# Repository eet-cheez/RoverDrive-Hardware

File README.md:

# RoverDrive-Hardware
A custom PCB for a robot powered by an esp32 microcontroller that has pins to control 4 servos plus one for sub-micro servo at 3.3v (in case it burns out at 5v). It also can support multiple other devices like LEDs or sensors and has an IMU to know its direction.

### Why am I doing this?
Last year, I built a robot that was controlled by connecting to an app. The problem is that the inside was a mess of wires and modules floating around, so it was a pain to fix and improve. I decided a PCB could fit more features while also being much easier to assemble and access.

## Details
- The microcontroller is an ESP32-S3-mini-1. I only really chose it because it seemed compact, but there are probably much better options. 
- For the IMU, it uses a BNO055, which does all of the calculations internally to find its orientation. Might be a bit overkill, but I want to make sure it works properly.
- The board uses a basic ams1117-3.3 to to power all of the 3.3v devices.
- Power is supplied to the board via a 1s lipo battery, which gets boosted to 5v by a mt3608 regulator.
- PCB designed in KiCad.
### Schematic: 

### PCB: 

#### CAD:
This is that the robot looks like with a model of the PCB (in TinkerCad):

The robot chassis needed to be changed to fit the PCB. Files have been attached if needed.

## BOM
| Item                  | Description         | Quantity | Cost |
|-----------------------|---------------------|----------|----------------|
|ESP32-S3-MINI-1-N8|	the microcontroller	|1	|$6.15 |
|NFM18PC104R1E3D|	100nf capacitor	|13	|$1.69|
|PTS647SN50SMTR2 LFS|	reset and boot buttons|	2	|$0.46|
|GRM188C81A226ME01D|	22uf ceramic capacitor|	3	|$0.87|
|TAJA226K010RNJ|	22uf tantalum capacitor. for ams1117-3.3	|2|$0.70|
|SS34| schottky diode	|1|$0.52|
|SRP7028AA-220M|	22uh inductor	for 5v regulator|1|$1.11|
|C1608X7T1A106M080AC|	10uf ceramic capacitor	|3|	$0.69|
|06031A220FAT2A|	22pf ceramic capacitor for gyro|3	|$1.32|
|CRCW060310K0FKEI|	10k resistor	|7	|$1.05|
|CRCW06035K10FKEC|	5.1k resistor	|3	|$0.36|
|RNCE0603BTE1K00|	1k resistor	|2|$0.42|
|ERJ-3RBD7501V|	7.5k resistor	|2|$0.30|
|ABS07-32.768KHZ-7-T|	32.768 kHz crystal for gyro|1|$0.82|
|BNO055|	9 axis IMU	|1|$12.34|
|USB4105-GF-A	|USB c receptacle, 16 contact|1|$0.78|
|MT3608|	boost converter. used to increase battery voltage to 5v (already have)|	1	|$0|
|AMS1117-3.3|	3.3v voltage regulator	|1	|$0|
|2.54mm pin headers	|for servos	|5| $0|
|Molex picoblade connector|fits with the battery, probably|1|$0|
|JST Connectors (2-pin, 3-pin, 4-pin)|Probably JST XH|3|$0|
|PCB|from JLCPCB|1|$41.71 **(See below for price explanation)***|
**Total:			$71.29**

Sheet with part links: https://docs.google.com/spreadsheets/d/1vR1n98YzZK8dJmbvGAbjTAVUf36cDbNLpNew4ql-z88/edit?usp=sharing

### * PCB Price Explanation
I'm exhibiting the full Roverdrive project at Open Sauce this year and did not have much time to create the hardware (need to finish by the 19th, difficult with Undercity taking up time). In order to get the PCB on time, I had to pay way more for shipping and couldn't spend much time optimizing the cost. I've already bought all of the parts, and I understand if Hack Club doesn't want to reimburse the full cost. If needed, I would gladly take a smaller, more reasonable reimbursement.

### Finished Project

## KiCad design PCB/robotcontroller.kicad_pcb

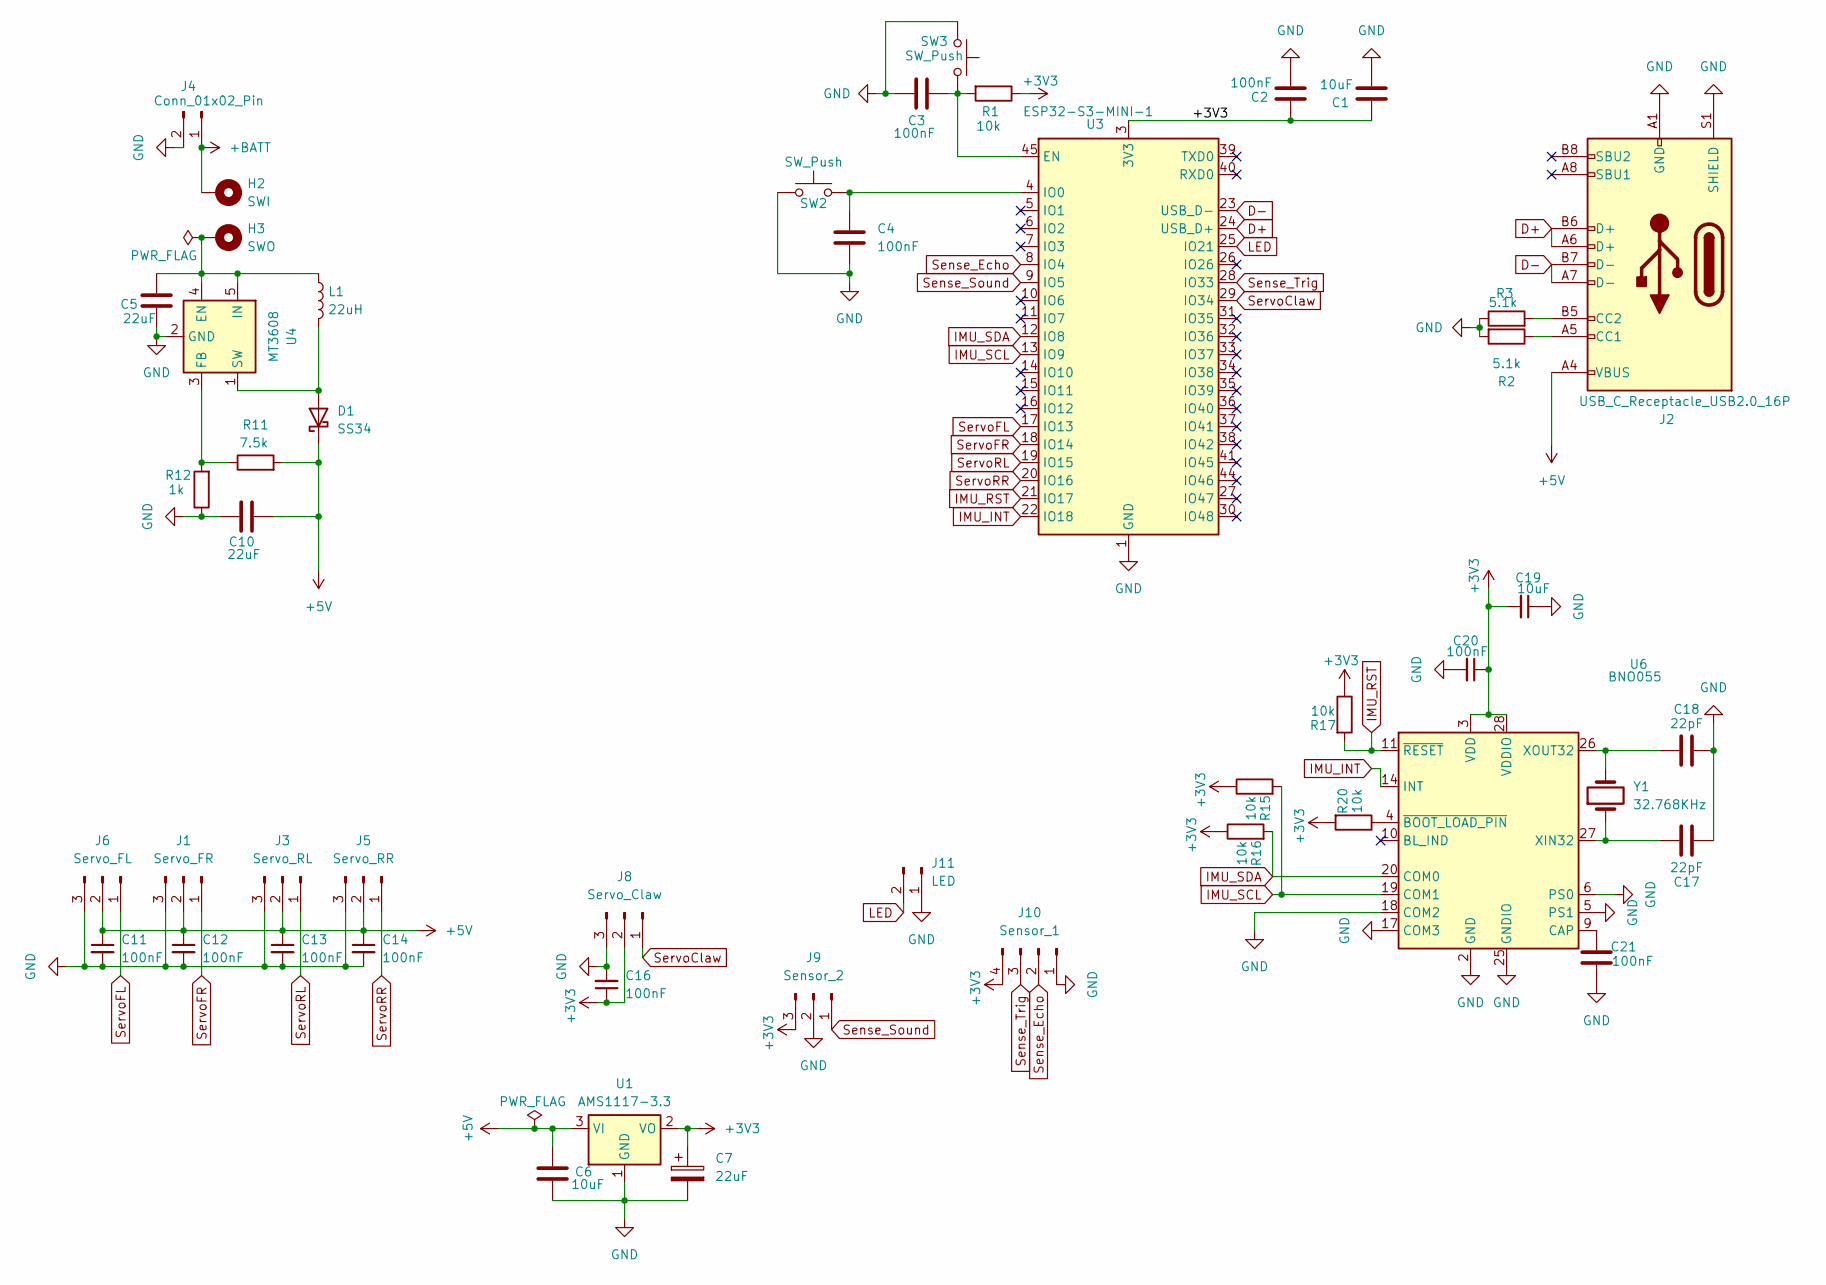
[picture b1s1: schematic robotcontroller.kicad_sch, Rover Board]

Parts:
C1, C6, C19: 10uF; C_0603_1608Metric
C2, C3, C4, C11, C12, C13, C14, C16, C20, C21: 100nF; C_0603_1608Metric
C5, C10: 22uF; C_0603_1608Metric
C7: 22uF; CP_EIA-3216-18_Kemet-A
C17, C18: 22pF; C_0603_1608Metric
D1: SS34; D_SMA
H2: SWI; SolderWire-1.5sqmm_1x01_D1.7mm_OD3mm
H3: SWO; SolderWire-1.5sqmm_1x01_D1.7mm_OD3mm
J1: Servo_FR; PinHeader_1x03_P2.54mm_Vertical
J2: USB_C_Receptacle_USB2.0_16P; USB_C_Receptacle_GCT_USB4105-xx-A_16P_TopMnt_Horizontal
J3: Servo_RL; PinHeader_1x03_P2.54mm_Vertical
J4: Conn_01x02_Pin; Molex_PicoBlade_53048-0210_1x02_P1.25mm_Horizontal
J5: Servo_RR; PinHeader_1x03_P2.54mm_Vertical
J6: Servo_FL; PinHeader_1x03_P2.54mm_Vertical
J8: Servo_Claw; PinHeader_1x03_P2.54mm_Vertical
J9: Sensor_2; JST_XH_B3B-XH-A_1x03_P2.50mm_Vertical
J10: Sensor_1; JST_XH_B4B-XH-A_1x04_P2.50mm_Vertical
J11: LED; JST_XH_B2B-XH-A_1x02_P2.50mm_Vertical
L1: 22uH; L_Bourns_SRP7028A_7.3x6.6mm
R1, R15, R16, R17, R20: 10k; R_0603_1608Metric
R2, R3: 5.1k; R_0603_1608Metric
R11: 7.5k; R_0603_1608Metric
R12: 1k; R_0603_1608Metric
SW2, SW3: SW_Push; SW_SPST_PTS647_Sx50
U1: AMS1117-3.3; SOT-223-3_TabPin2
U3: ESP32-S3-MINI-1; ESP32-S2-MINI-1
U4: MT3608; SOT-23-6
U6: BNO055; LGA-28_5.2x3.8mm_P0.5mm
Y1: 32.768KHz; XTAL_ABS07-32.768KHZ-7-T

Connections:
+3V3: C1.1, C2.1, C7.1, C16.1, C19.2, C20.1, J8.2, J9.3, J10.4, R1.1, R15.1, R16.1, R17.1, R20.2, U1.2 (VO), U3.3 (3V3), U6.3 (VDD), U6.28 (VDDIO)
+5V: C6.2, C10.2, C11.1, C12.1, C13.1, C14.1, D1.1 (K), J1.2, J2.A4 (VBUS), J2.A9 (VBUS), J2.B4 (VBUS), J2.B9 (VBUS), J3.2, J5.2, J6.2, R11.2, U1.3 (VI)
+BATT: H2.1, J4.1
D+: J2.A6 (D+), J2.B6 (D+), U3.24 (USB_D+)
D-: J2.A7 (D-), J2.B7 (D-), U3.23 (USB_D-)
GND: C1.2, C2.2, C3.2, C4.2, C5.1, C6.1, C7.2, C10.1, C11.2, C12.2, C13.2, C14.2, C16.2, C17.1, C18.2, C19.1, C20.2, C21.2, J1.3, J2.A1 (GND), J2.A12 (GND), J2.B1 (GND), J2.B12 (GND), J2.S1 (SHIELD), J3.3, J4.2, J5.3, J6.3, J8.3, J9.2, J10.1, J11.1, R2.2, R3.1, R12.1, SW2.1, SW3.1, U1.1 (GND), U3.1 (GND), U3.2 (GND), U3.42 (GND), U3.43 (GND), U3.46 (GND), U3.47 (GND), U3.48 (GND), U3.49 (GND), U3.50 (GND), U3.51 (GND), U3.52 (GND), U3.53 (GND), U3.54 (GND), U3.55 (GND), U3.56 (GND), U3.57 (GND), U3.58 (GND), U3.59 (GND), U3.60 (GND), U3.61 (GND), U3.62 (GND), U3.63 (GND), U3.64 (GND), U3.65 (GND), U4.2 (GND), U6.2 (GND), U6.5 (PS1), U6.6 (PS0), U6.17 (COM3), U6.18 (COM2), U6.25 (GNDIO)
IMU_INT: U3.22 (IO18), U6.14 (INT)
IMU_RST: R17.2, U3.21 (IO17), U6.11 (~RESET)
IMU_SCL: R15.2, U3.13 (IO9), U6.19 (COM1)
IMU_SDA: R16.2, U3.12 (IO8), U6.20 (COM0)
LED: J11.2, U3.25 (IO21)
unnamed: D1.2 (A), L1.2, U4.1 (SW)
unnamed: J2.A5 (CC1), R2.1
unnamed: J2.B5 (CC2), R3.2
unnamed: C3.1, R1.2, SW3.2, U3.45 (EN)
unnamed: C4.1, SW2.2, U3.4 (IO0)
unnamed: C5.2, H3.1, L1.1, U4.4 (EN), U4.5 (IN)
unnamed: R11.1, R12.2, U4.3 (FB)
unnamed: C21.1, U6.9 (CAP)
unnamed: C17.2, U6.27 (XIN32), Y1.1
unnamed: C18.1, U6.26 (XOUT32), Y1.2
unnamed: R20.1, U6.4 (~BOOT_LOAD_PIN)
Sense_Echo: J10.2, U3.8 (IO4)
Sense_Sound: J9.1, U3.9 (IO5)
Sense_Trig: J10.3, U3.28 (IO33)
ServoClaw: J8.1, U3.29 (IO34)
ServoFL: J6.1, U3.17 (IO13)
ServoFR: J1.1, U3.18 (IO14)
ServoRL: J3.1, U3.19 (IO15)
ServoRR: J5.1, U3.20 (IO16)

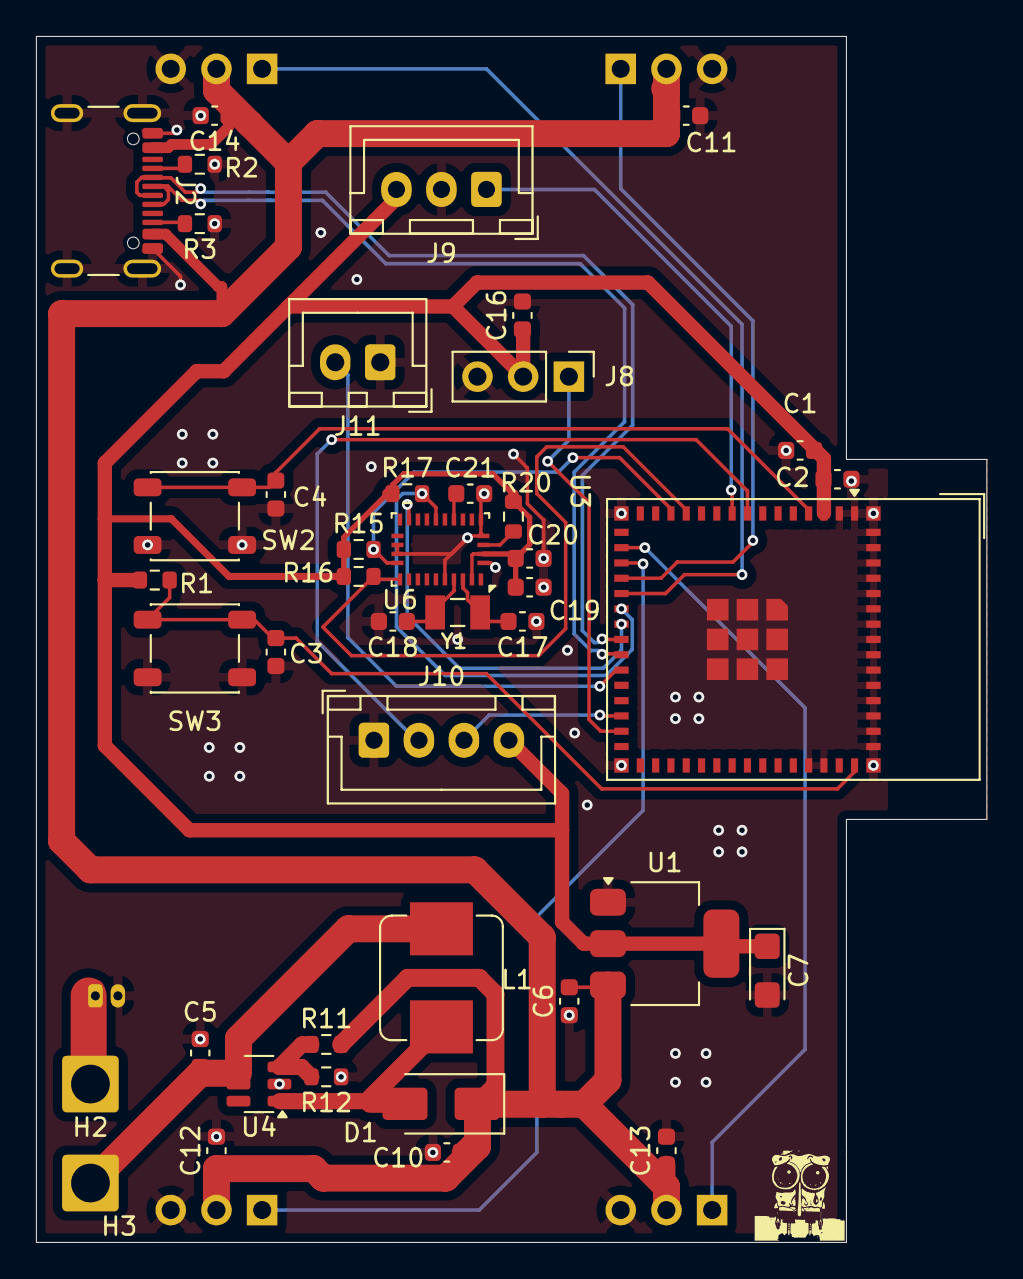
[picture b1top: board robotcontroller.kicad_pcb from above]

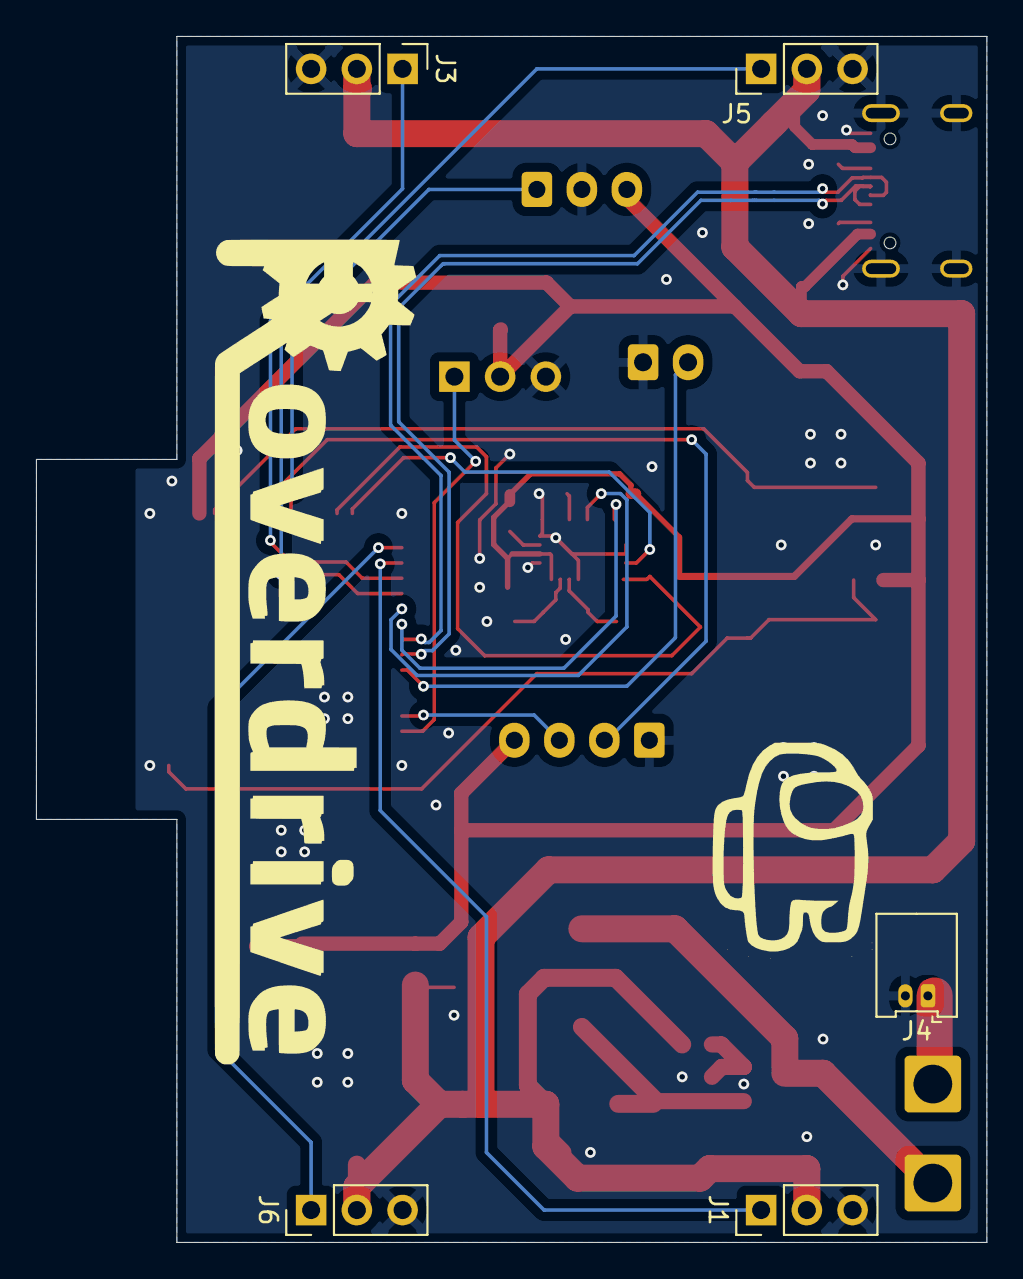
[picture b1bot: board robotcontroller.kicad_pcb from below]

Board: 2 copper layers, 52.8 x 67.0 mm, 48 parts (5 on the bottom side), 30 nets.

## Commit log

2025-07-31 add cad
2025-08-01 improve step
